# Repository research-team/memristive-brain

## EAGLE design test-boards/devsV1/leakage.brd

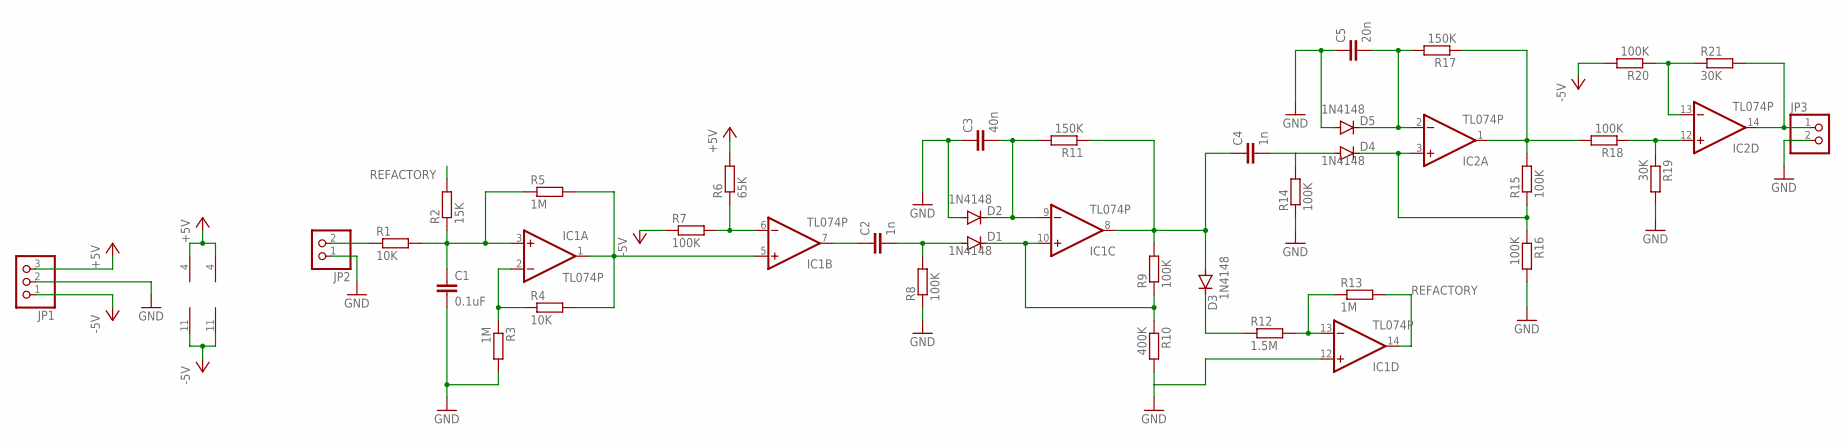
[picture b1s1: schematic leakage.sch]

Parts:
C1: 0.1uF; C025-025X050
C2, C4: 1n; C025-025X050
C3: 40n; C025-025X050
C5: 20n; C025-025X050
D1, D2, D3, D4, D5: 1N4148; DO35-10
IC1, IC2: TL074P; DIL14
JP1: PINHD-1X3; 1X03
JP2, JP3: PINHD-1X2; 1X02
R1, R4: 10K; 0207/10
R2: 15K; 0207/10
R3, R5, R13: 1M; 0207/10
R6: 65K; 0207/10
R7, R8, R9, R14, R15, R16, R18, R20: 100K; 0207/10
R10: 400K; 0207/10
R11, R17: 150K; 0207/10
R12: 1.5M; 0207/10
R19, R21: 30K; 0207/10

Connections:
+5V: IC1.4 (V+), IC2.4 (V+), JP1.3, R6.2
-5V: IC1.11 (V-), IC2.11 (V-), JP1.1, R7.1, R20.2
GND: C1.2, C3.1, C5.1, D2.A, D5.A, IC1.12 (+IN), JP1.2, JP2.1, JP3.2, R3.2, R8.1, R10.2, R14.1, R16.2, R19.2
unnamed: C1.1, IC1.3 (+IN), R1.2, R2.1, R5.1
unnamed: IC1.2 (-IN), R3.1, R4.1
unnamed: IC1.1 (OUT), IC1.5 (+IN), R4.2, R5.2
unnamed: JP2.2, R1.1
unnamed: IC1.6 (-IN), R6.1, R7.2
unnamed: C2.1, IC1.7 (OUT)
unnamed: C2.2, D1.A, R8.2
unnamed: D1.C, IC1.10 (+IN), R9.1, R10.1
unnamed: C4.1, D3.A, IC1.8 (OUT), R9.2, R11.1
unnamed: C3.2, D2.C, IC1.9 (-IN), R11.2
unnamed: IC1.13 (-IN), R12.2, R13.1
unnamed: D3.C, R12.1
unnamed: IC2.12 (+IN), R18.1, R19.1
unnamed: C4.2, D4.A, R14.2
unnamed: D4.C, IC2.3 (+IN), R15.1, R16.1
unnamed: IC2.1 (OUT), R15.2, R17.1, R18.2
unnamed: C5.2, D5.C, IC2.2 (-IN), R17.2
unnamed: IC2.13 (-IN), R20.1, R21.1
unnamed: IC2.14 (OUT), JP3.1, R21.2
REFACTORY: IC1.14 (OUT), R2.2, R13.2

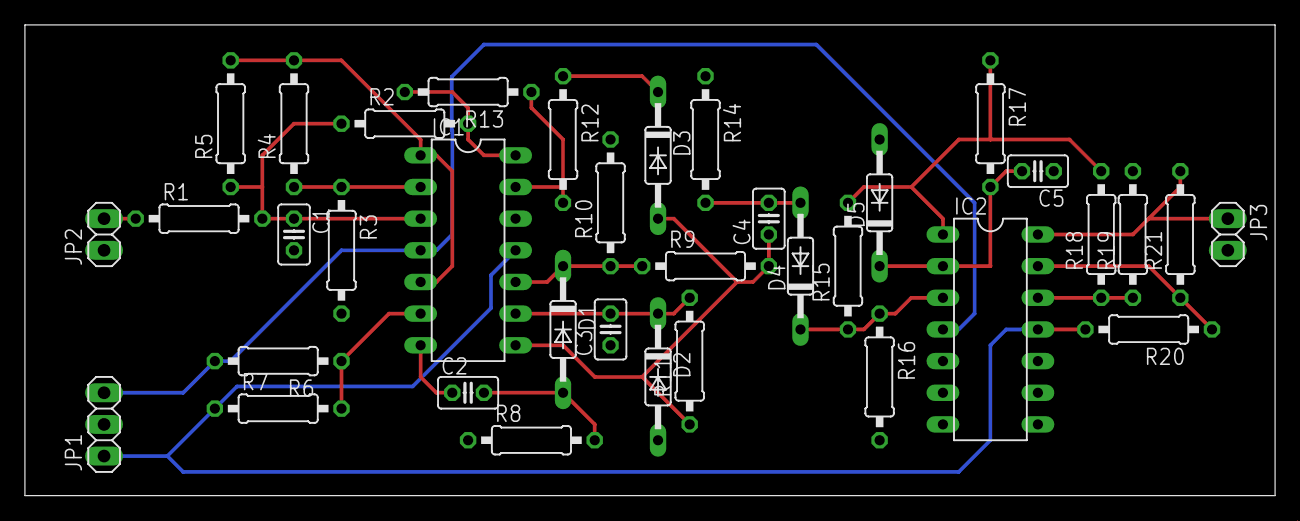
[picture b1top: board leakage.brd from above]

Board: 2 copper layers, 100.3 x 37.8 mm, 36 parts (0 on the bottom side), 23 nets.

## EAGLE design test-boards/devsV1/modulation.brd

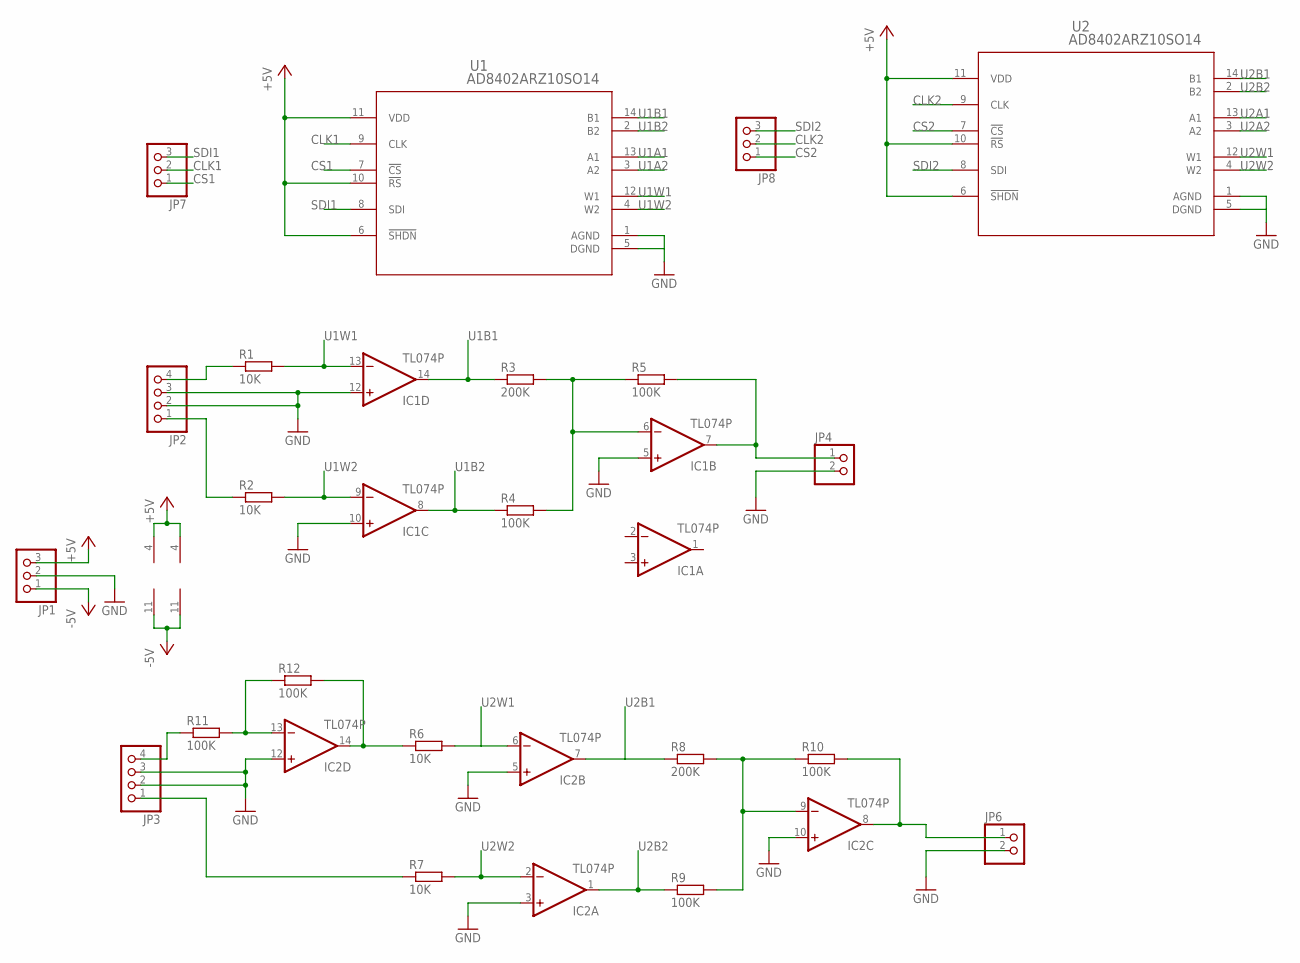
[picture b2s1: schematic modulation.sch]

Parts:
IC1, IC2: TL074P; DIL14
JP1, JP7, JP8: PINHD-1X3; 1X03
JP2, JP3: PINHD-1X4; 1X04
JP4, JP6: PINHD-1X2; 1X02
R1, R2, R6, R7: 10K; 0207/7
R3, R8: 200K; 0207/7
R4, R5, R9, R10, R11, R12: 100K; 0207/7
U1, U2: AD8402ARZ10SO14; SO14

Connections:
+5V: IC1.4 (V+), IC2.4 (V+), JP1.3, U1.6 (!SHDN), U1.10 (!RS), U1.11 (VDD), U2.6 (!SHDN), U2.10 (!RS), U2.11 (VDD)
-5V: IC1.11 (V-), IC2.11 (V-), JP1.1
CLK1: JP7.2, U1.9 (CLK)
CLK2: JP8.2, U2.9 (CLK)
CS1: JP7.1, U1.7 (!CS)
CS2: JP8.1, U2.7 (!CS)
GND: IC1.5 (+IN), IC1.10 (+IN), IC1.12 (+IN), IC2.3 (+IN), IC2.5 (+IN), IC2.10 (+IN), IC2.12 (+IN), JP1.2, JP2.2, JP2.3, JP3.2, JP3.3, JP4.2, JP6.2, U1.1 (AGND), U1.5 (DGND), U2.1 (AGND), U2.5 (DGND)
unnamed: IC1.6 (-IN), R3.2, R4.2, R5.1
unnamed: JP2.4, R1.1
unnamed: JP2.1, R2.1
unnamed: IC2.14 (OUT), R6.1, R12.2
unnamed: IC1.7 (OUT), JP4.1, R5.2
unnamed: JP3.1, R7.1
unnamed: IC2.9 (-IN), R8.2, R9.2, R10.1
unnamed: IC2.8 (OUT), JP6.1, R10.2
unnamed: JP3.4, R11.1
unnamed: IC2.13 (-IN), R11.2, R12.1
SDI1: JP7.3, U1.8 (SDI)
SDI2: JP8.3, U2.8 (SDI)
U1A1: U1.13 (A1)
U1A2: U1.3 (A2)
U1B1: IC1.14 (OUT), R3.1, U1.14 (B1)
U1B2: IC1.8 (OUT), R4.1, U1.2 (B2)
U1W1: IC1.13 (-IN), R1.2, U1.12 (W1)
U1W2: IC1.9 (-IN), R2.2, U1.4 (W2)
U2A1: U2.13 (A1)
U2A2: U2.3 (A2)
U2B1: IC2.7 (OUT), R8.1, U2.14 (B1)
U2B2: IC2.1 (OUT), R9.1, U2.2 (B2)
U2W1: IC2.6 (-IN), R6.2, U2.12 (W1)
U2W2: IC2.2 (-IN), R7.2, U2.4 (W2)

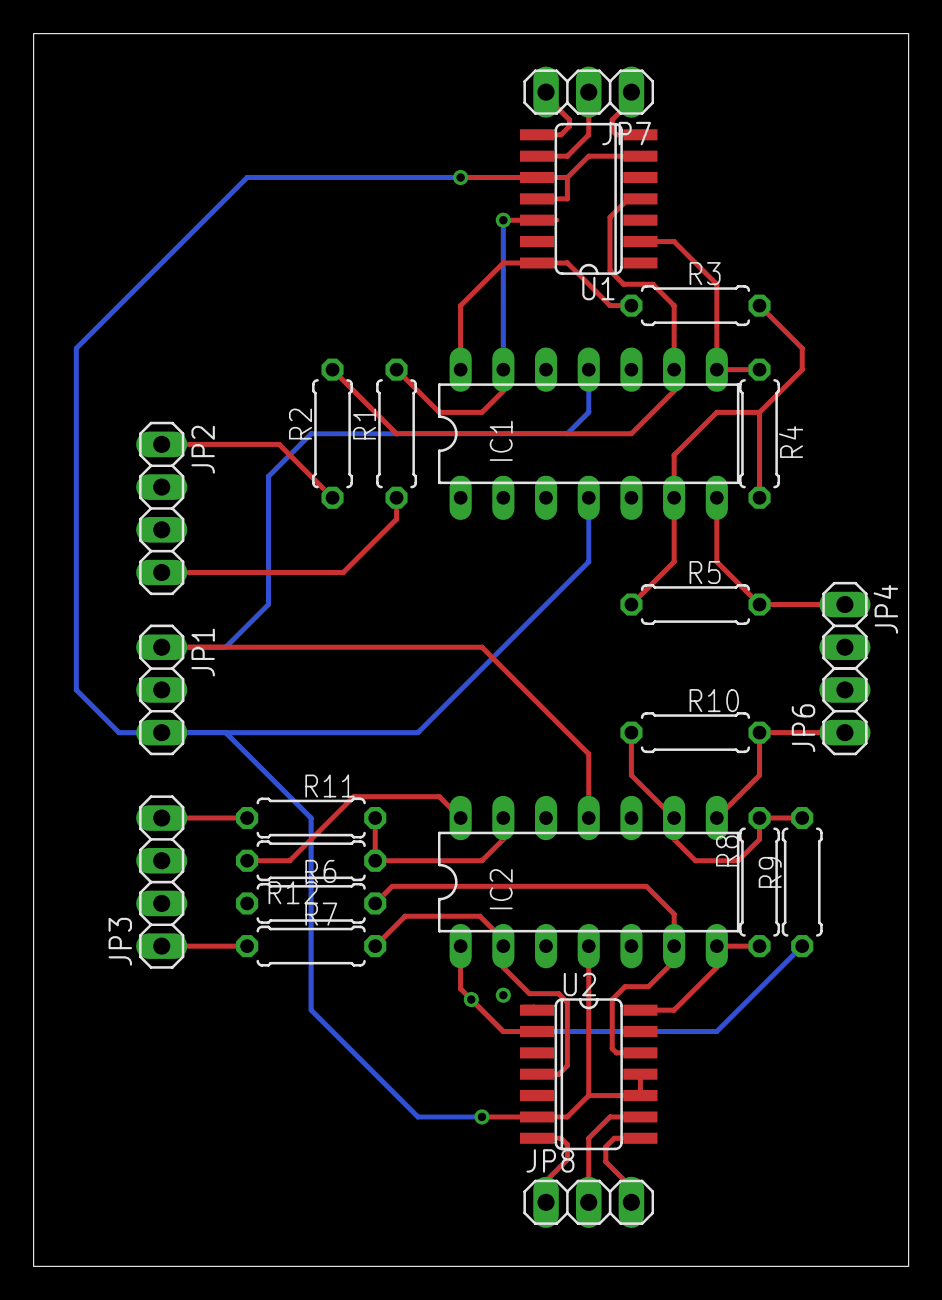
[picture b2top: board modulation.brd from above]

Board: 2 copper layers, 52.0 x 73.3 mm, 23 parts (0 on the bottom side), 27 nets.
